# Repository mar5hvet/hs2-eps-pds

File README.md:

# hs2-eps-pds
Repository for EPS KiCad design files, including schematics, PCB layouts, and documentation.

Uploaded by Chase

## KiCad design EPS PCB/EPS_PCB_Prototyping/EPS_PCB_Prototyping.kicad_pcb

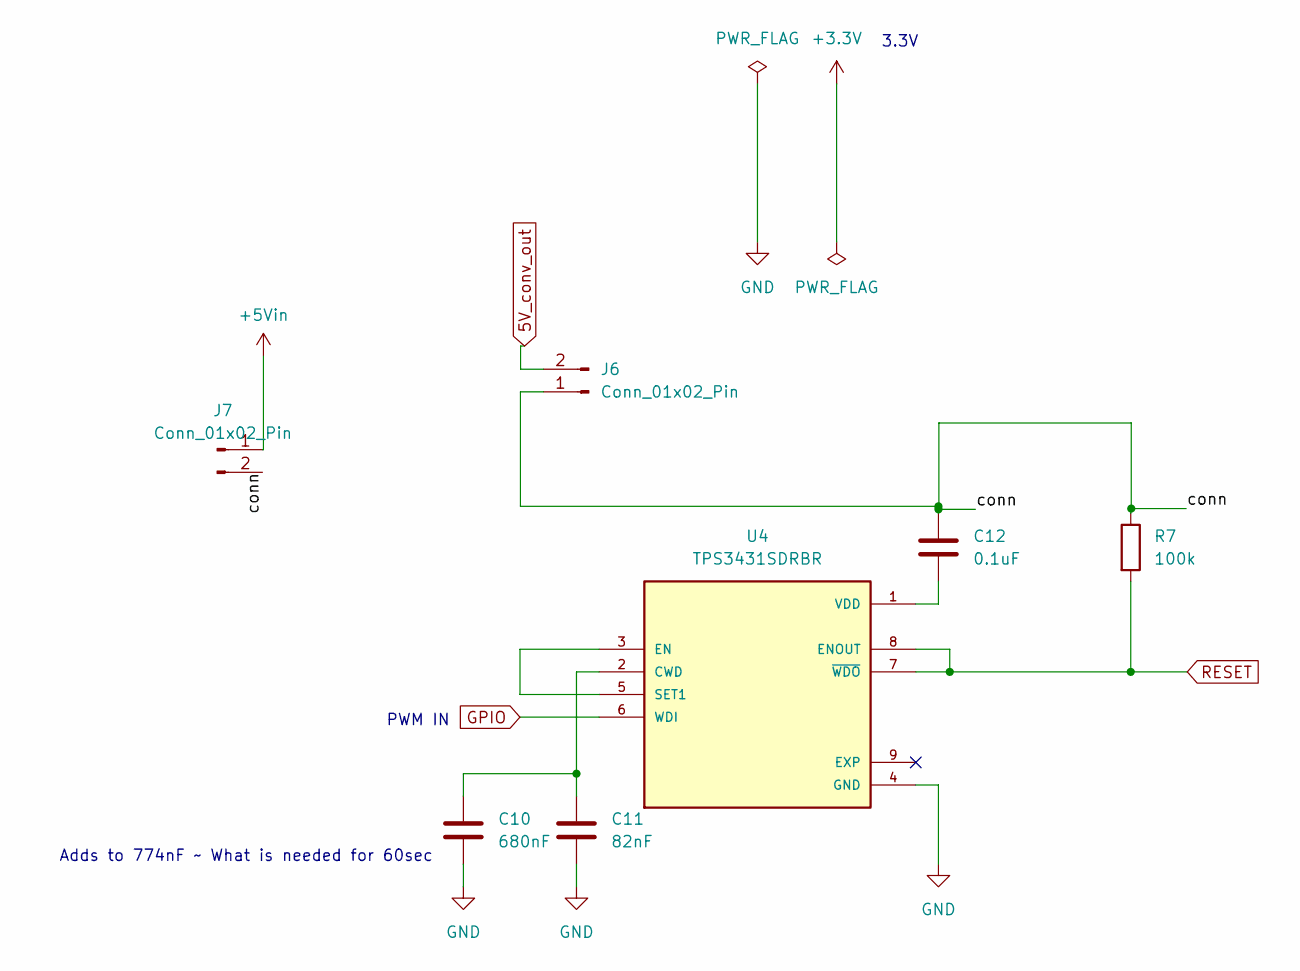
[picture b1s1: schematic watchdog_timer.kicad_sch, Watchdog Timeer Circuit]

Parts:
C10: 680nF; C_1206_3216Metric
C11: 82nF; C_1206_3216Metric
C12: 0.1uF; C_0603_1608Metric
J6, J7: Conn_01x02_Pin; PinSocket_1x02_P2.54mm_Vertical
R7: 100k; R_1206_3216Metric
U4: TPS3431SDRBR; IC_TPS3431SDRBR; PARTREV A

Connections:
5V_conv_out: J6.2; also elsewhere on the board
+5Vin: J7.1
/watchdog_timer/conn: C12.1, J6.1, J7.2, R7.1
GND: C10.2, C11.2, U4.4 (GND); also elsewhere on the board
GPIO: U4.6 (WDI); also elsewhere on the board
unnamed: C10.1, C11.1, U4.2 (CWD)
unnamed: U4.3 (EN), U4.5 (SET1)
unnamed: C12.2, U4.1 (VDD)
RESET: R7.2, U4.7 (~WDO), U4.8 (ENOUT); also elsewhere on the board

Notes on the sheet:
PWM IN
3.3V
Adds to 774nF ~ What is needed for 60sec

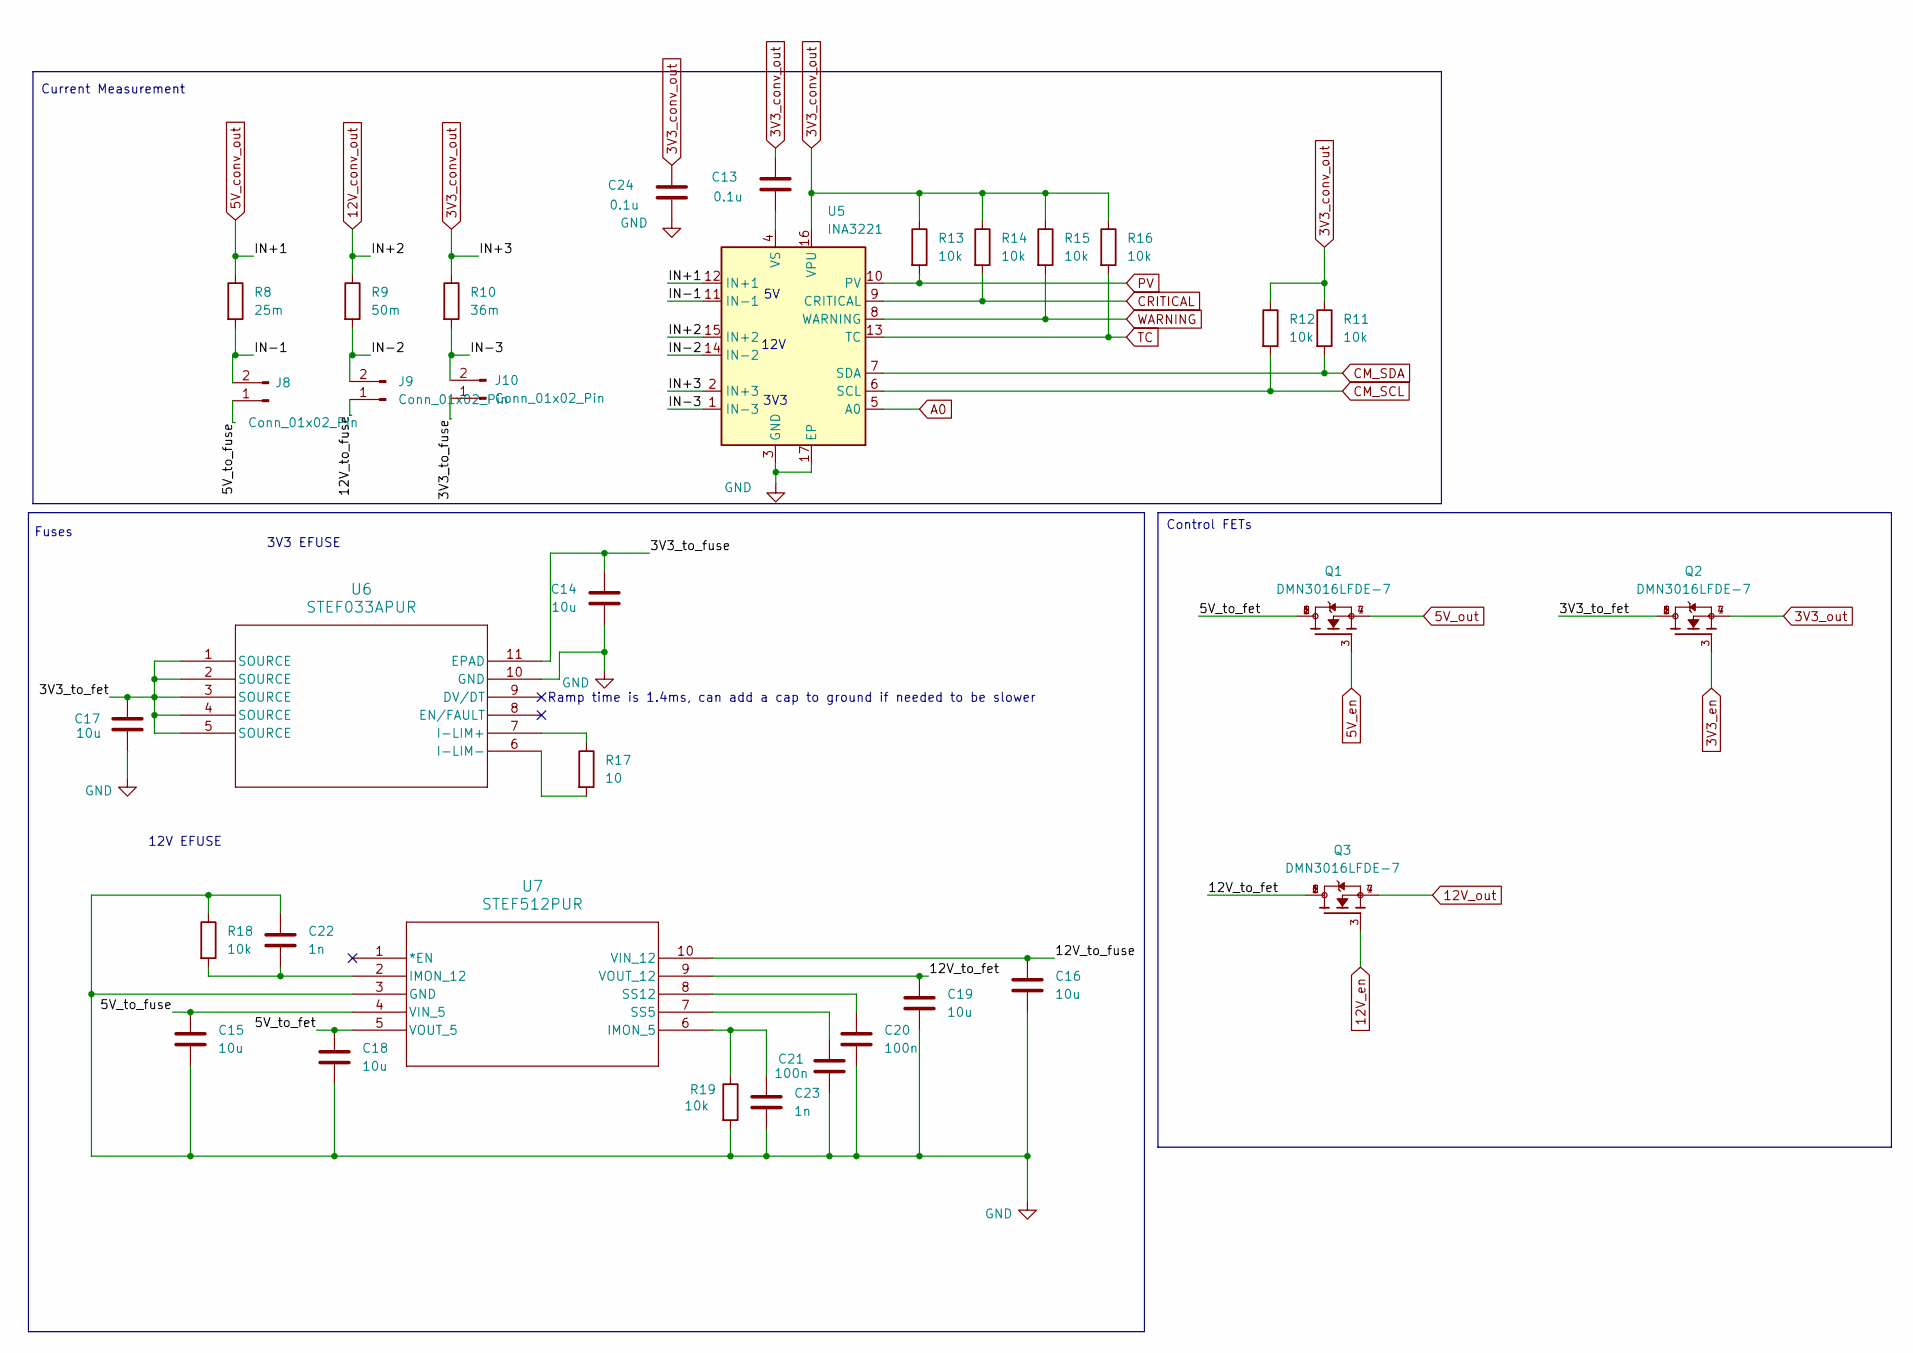
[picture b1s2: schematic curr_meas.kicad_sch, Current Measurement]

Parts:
C13, C24: 0.1u; C_0603_1608Metric
C14, C15, C16, C17, C18, C19: 10u; C_0603_1608Metric
C20, C21: 100n; C_0603_1608Metric
C22, C23: 1n; C_0603_1608Metric
J8, J9, J10: Conn_01x02_Pin; PinSocket_1x02_P2.54mm_Vertical
Q1, Q2, Q3: DMN3016LFDE-7; TRANS_DMN3016LFDE-7; PARTREV 2-2
R8: 25m; RES_VISHAY_WSLP2512_A_VIS
R9: 50m; RES_VISHAY_WSLP2512_A_VIS
R10: 36m; RES_VISHAY_WSLP2512_A_VIS
R11, R12, R13, R14, R15, R16, R18, R19: 10k; R_0603_1608Metric
R17: 10; R_0603_1608Metric
U5: INA3221; Texas_RGV0016A_VQFN-16-1EP_4x4mm_P0.65mm_EP2.1x2.1mm
U6: STEF033APUR; STEF033
U7: STEF512PUR; STEF512

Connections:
3V3_conv_out: C13.1, C24.1, R10.1, R11.1, R12.1, R13.1, R14.1, R15.1, R16.1, U5.2 (IN+3), U5.16 (VPU); also elsewhere on the board
3V3_en: Q2.3; also elsewhere on the board
3V3_out: Q2.4, Q2.7; also elsewhere on the board
5V_conv_out: R8.1, U5.12 (IN+1); also elsewhere on the board
5V_en: Q1.3; also elsewhere on the board
5V_out: Q1.4, Q1.7; also elsewhere on the board
12V_conv_out: R9.1, U5.15 (IN+2); also elsewhere on the board
12V_en: Q3.3; also elsewhere on the board
12V_out: Q3.4, Q3.7; also elsewhere on the board
/Curr_meas/3V3_to_fet: C17.1, Q2.1, Q2.2, Q2.5, Q2.6, U6.1 (SOURCE), U6.2 (SOURCE), U6.3 (SOURCE), U6.4 (SOURCE), U6.5 (SOURCE)
/Curr_meas/3V3_to_fuse: C14.1, J10.1, U6.11 (EPAD)
/Curr_meas/5V_to_fet: C18.1, Q1.1, Q1.2, Q1.5, Q1.6, U7.5 (VOUT_5)
/Curr_meas/5V_to_fuse: C15.1, J8.1, U7.4 (VIN_5)
/Curr_meas/12V_to_fet: C19.1, Q3.1, Q3.2, Q3.5, Q3.6, U7.9 (VOUT_12)
/Curr_meas/12V_to_fuse: C16.1, J9.1, U7.10 (VIN_12)
/Curr_meas/IN-1: J8.2, R8.2, U5.11 (IN-1)
/Curr_meas/IN-2: J9.2, R9.2, U5.14 (IN-2)
/Curr_meas/IN-3: J10.2, R10.2, U5.1 (IN-3)
A0: U5.5 (A0); also elsewhere on the board
CM_SCL: R12.2, U5.6 (SCL); also elsewhere on the board
CM_SDA: R11.2, U5.7 (SDA); also elsewhere on the board
CRITICAL: R14.2, U5.9 (CRITICAL); also elsewhere on the board
GND: C14.2, C15.2, C16.2, C17.2, C18.2, C19.2, C20.2, C21.2, C22.1, C23.2, C24.2, R18.1, R19.2, U5.3 (GND), U5.17 (EP), U6.10 (GND), U7.3 (GND); also elsewhere on the board
unnamed: C13.2, U5.4 (VS)
unnamed: R17.1, U6.7 (I-LIM+)
unnamed: R17.2, U6.6 (I-LIM-)
unnamed: C23.1, R19.1, U7.6 (IMON_5)
unnamed: C22.2, R18.2, U7.2 (IMON_12)
unnamed: C21.1, U7.7 (SS5)
unnamed: C20.1, U7.8 (SS12)
PV: R13.2, U5.10 (PV); also elsewhere on the board
TC: R16.2, U5.13 (TC)
WARNING: R15.2, U5.8 (WARNING); also elsewhere on the board

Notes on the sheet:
12V
Current Measurement
3V3 EFUSE
3V3
Ramp time is 1.4ms, can add a cap to ground if needed to be slower
12V EFUSE
Control FETs
Fuses

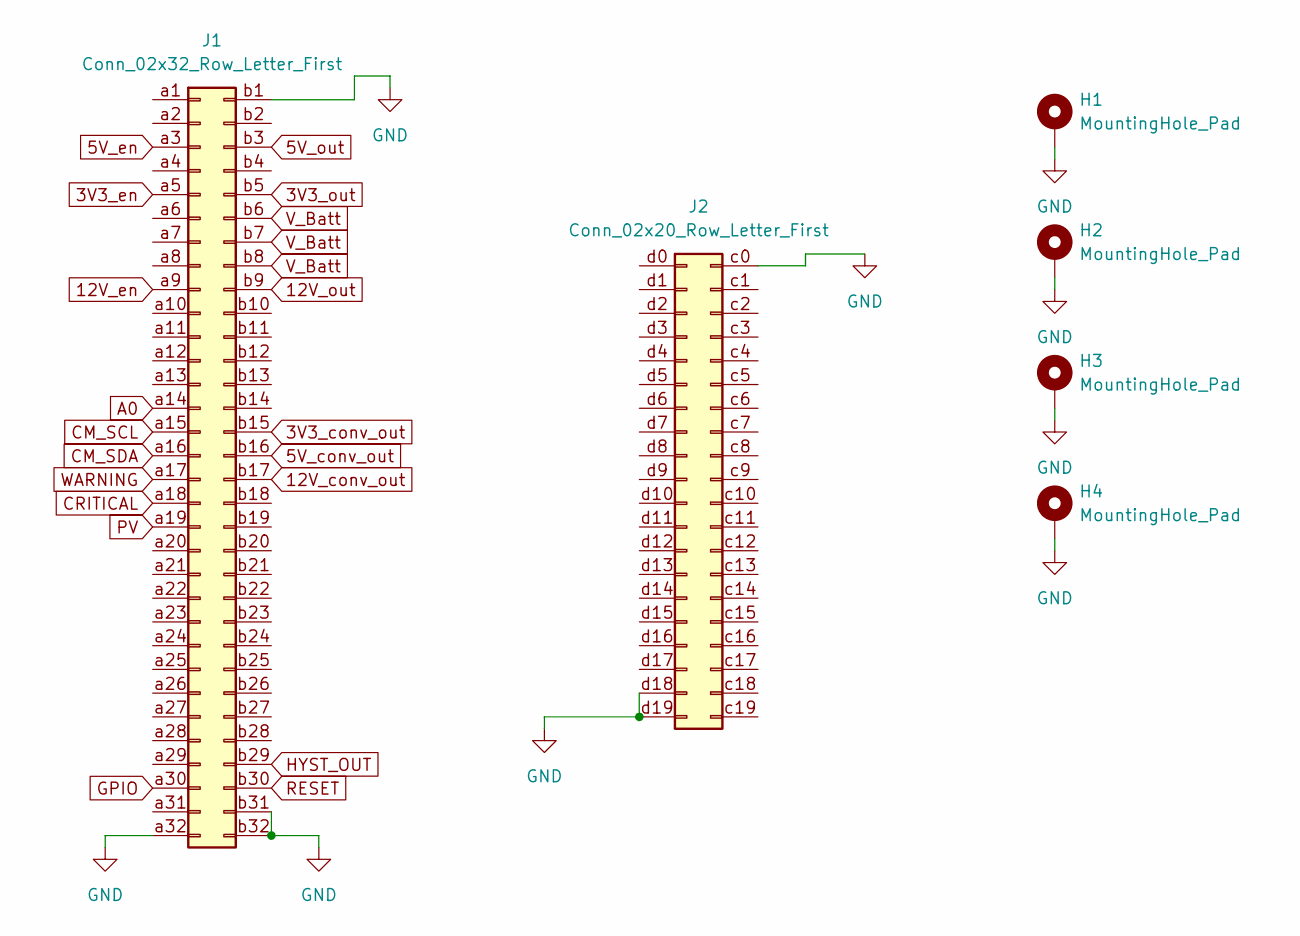
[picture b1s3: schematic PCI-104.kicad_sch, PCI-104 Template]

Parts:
H1, H2, H3, H4: MountingHole_Pad; MountingHole_3.2mm_M3_Pad
J1: Conn_02x32_Row_Letter_First; PinSocket_2x32_P2.54mm_Vertical
J2: Conn_02x20_Row_Letter_First; PinSocket_2x20_P2.54mm_Vertical

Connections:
3V3_conv_out: J1.b15; also elsewhere on the board
3V3_en: J1.a5; also elsewhere on the board
3V3_out: J1.b5; also elsewhere on the board
5V_conv_out: J1.b16; also elsewhere on the board
5V_en: J1.a3; also elsewhere on the board
5V_out: J1.b3; also elsewhere on the board
12V_conv_out: J1.b17; also elsewhere on the board
12V_en: J1.a9; also elsewhere on the board
12V_out: J1.b9; also elsewhere on the board
A0: J1.a14; also elsewhere on the board
CM_SCL: J1.a15; also elsewhere on the board
CM_SDA: J1.a16; also elsewhere on the board
CRITICAL: J1.a18; also elsewhere on the board
GND: H1.1, H2.1, H3.1, H4.1, J1.a32, J1.b1, J1.b31, J1.b32, J2.c0, J2.d18, J2.d19; also elsewhere on the board
GPIO: J1.a30; also elsewhere on the board
HYST_OUT: J1.b29; also elsewhere on the board
PV: J1.a19; also elsewhere on the board
RESET: J1.b30; also elsewhere on the board
V_Batt: J1.b6, J1.b7, J1.b8; also elsewhere on the board
WARNING: J1.a17; also elsewhere on the board

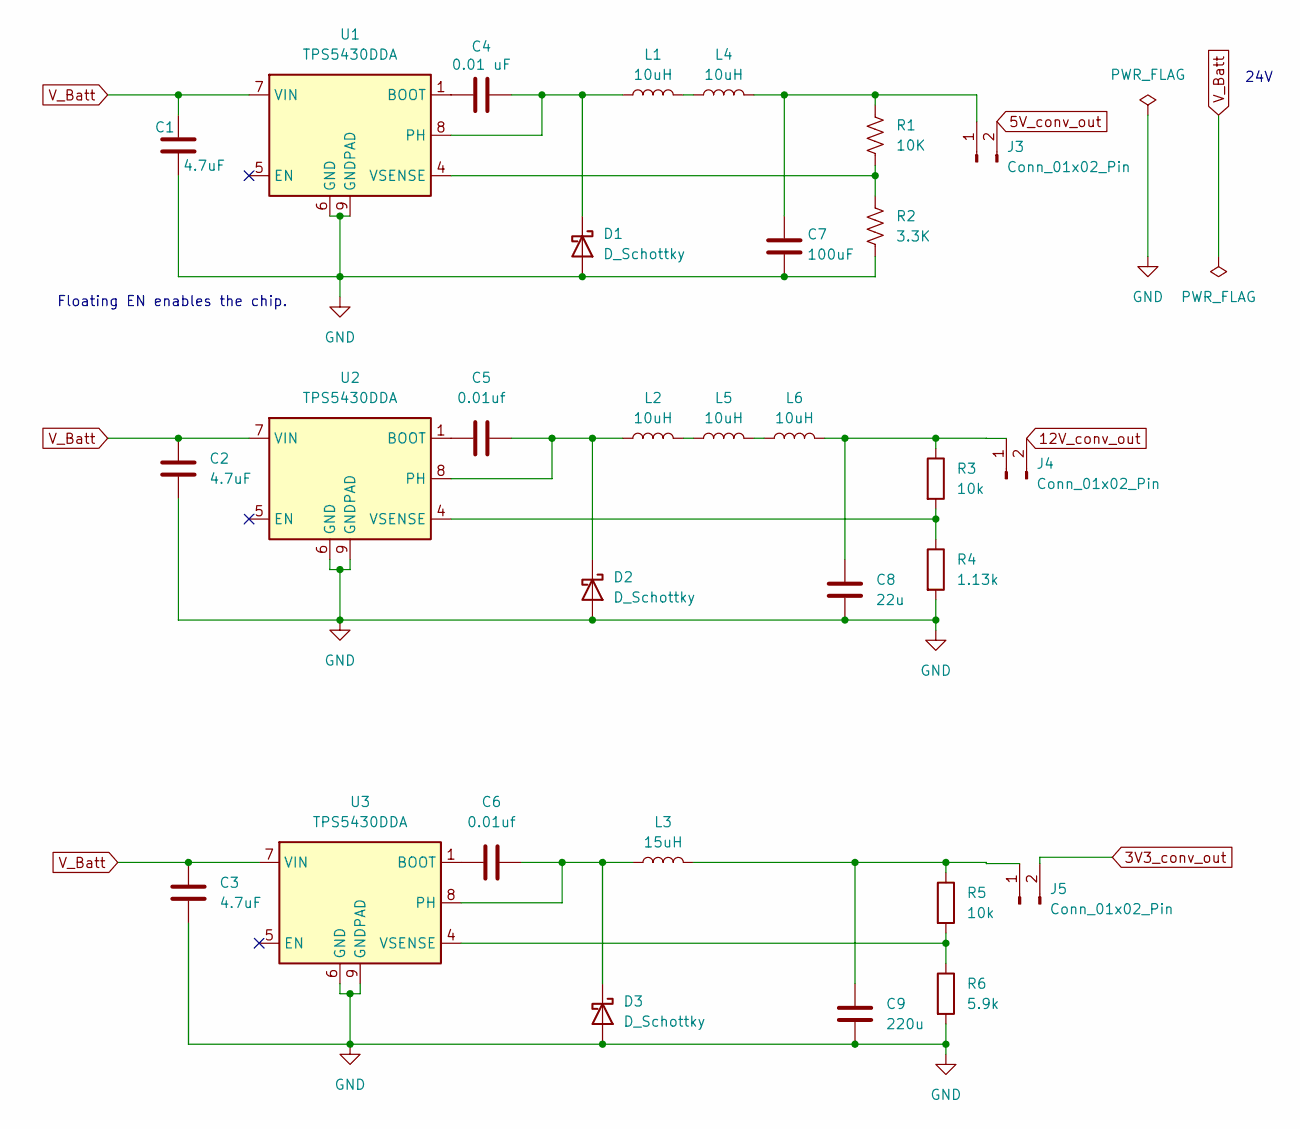
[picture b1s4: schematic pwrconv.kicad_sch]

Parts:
C1, C2, C3: 4.7uF; C_0805_2012Metric; LCSC C1779
C4: 0.01 uF; C_0603_1608Metric; LCSC C1589
C5, C6: 0.01uf; C_0603_1608Metric; LCSC C1589
C7: 100uF; C_0805_2012Metric; LCSC C2836437
C8: 22u; C_0805_2012Metric; LCSC C45783
C9: 220u; C_0805_2012Metric; LCSC C125977
D1, D2, D3: D_Schottky; D_SOD-323; LCSC C191023
J3, J4, J5: Conn_01x02_Pin; PinSocket_1x02_P2.54mm_Vertical
L1, L2, L4, L5, L6: 10uH; L_Changjiang_FXL0630; LCSC C167223
L3: 15uH; L_Changjiang_FXL0630; LCSC C40000
R1: 10K; R_0603_1608Metric; LCSC C15401
R2: 3.3K; R_1206_3216Metric; LCSC C26041
R3, R5: 10k; R_0603_1608Metric; LCSC C15401
R4: 1.13k; R_1206_3216Metric; LCSC C4410
R6: 5.9k; R_1206_3216Metric; LCSC C488883
U1, U2, U3: TPS5430DDA; TI_SO-PowerPAD-8_ThermalVias; LCSC C9864

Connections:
3V3_conv_out: J5.2; also elsewhere on the board
5V_conv_out: J3.2; also elsewhere on the board
12V_conv_out: J4.2; also elsewhere on the board
GND: C1.2, C2.2, C3.2, C7.2, C8.1, C9.1, D1.2 (A), D2.2 (A), D3.2 (A), R2.2, R4.2, R6.2, U1.6 (GND), U1.9 (GNDPAD), U2.6 (GND), U2.9 (GNDPAD), U3.6 (GND), U3.9 (GNDPAD); also elsewhere on the board
unnamed: C4.2, D1.1 (K), L1.1, U1.8 (PH)
unnamed: C5.2, D2.1 (K), L2.1, U2.8 (PH)
unnamed: C6.2, D3.1 (K), L3.1, U3.8 (PH)
unnamed: C7.1, J3.1, L4.2, R1.1
unnamed: C8.2, J4.1, L6.2, R3.1
unnamed: C9.2, J5.1, L3.2, R5.1
unnamed: L1.2, L4.1
unnamed: L2.2, L5.1
unnamed: L5.2, L6.1
unnamed: C4.1, U1.1 (BOOT)
unnamed: R1.2, R2.1, U1.4 (VSENSE)
unnamed: C5.1, U2.1 (BOOT)
unnamed: R3.2, R4.1, U2.4 (VSENSE)
unnamed: C6.1, U3.1 (BOOT)
unnamed: R5.2, R6.1, U3.4 (VSENSE)
V_Batt: C1.1, C2.1, C3.1, U1.7 (VIN), U2.7 (VIN), U3.7 (VIN); also elsewhere on the board

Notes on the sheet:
24V
Floating EN enables the chip.

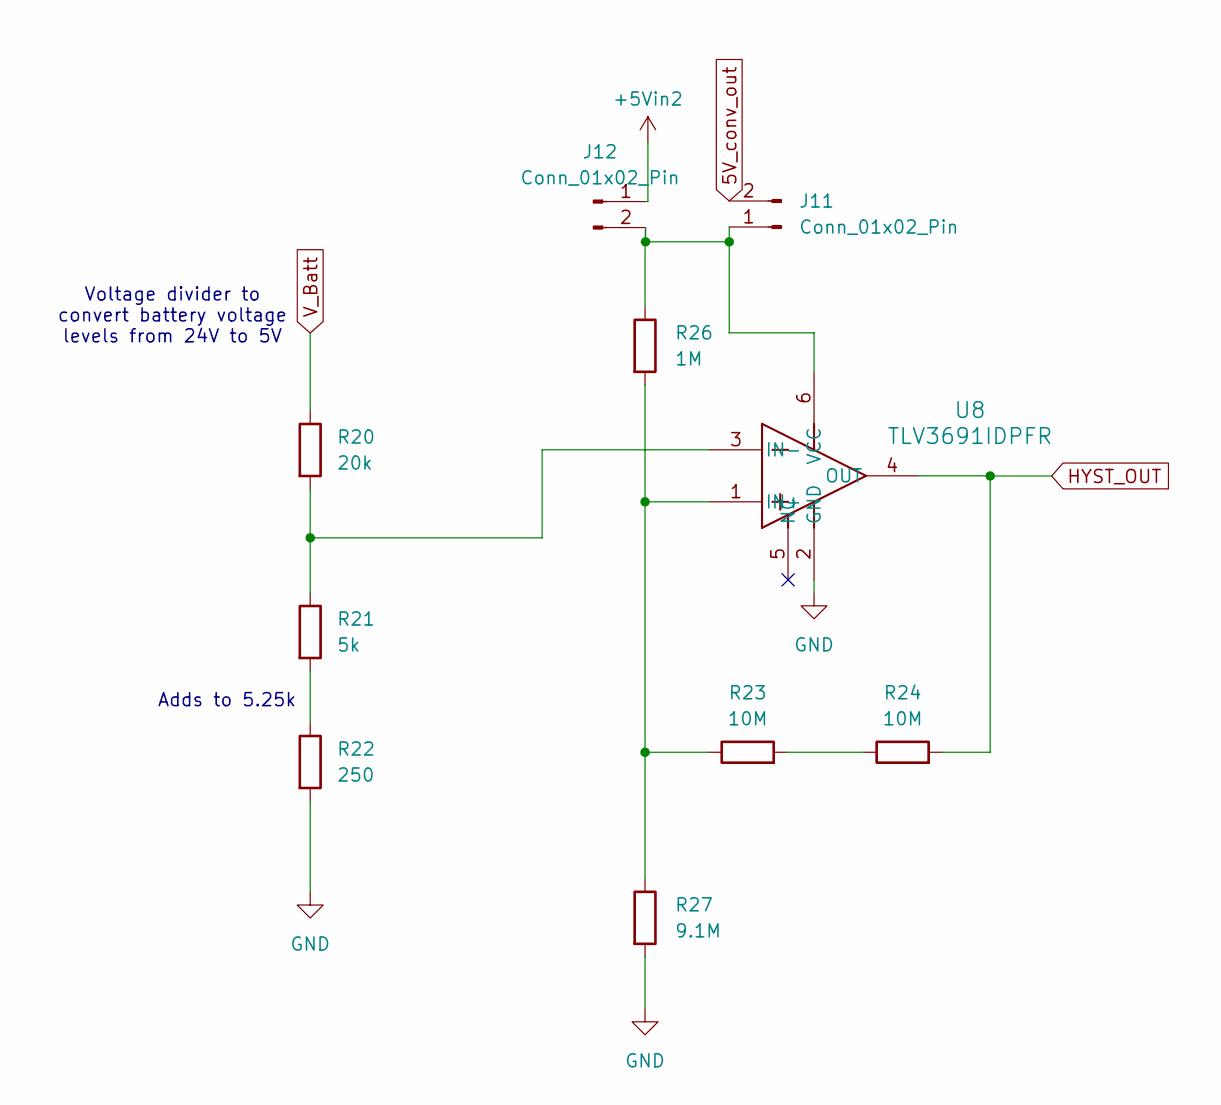
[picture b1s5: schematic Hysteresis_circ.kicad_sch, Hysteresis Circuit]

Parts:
J11, J12: Conn_01x02_Pin; PinSocket_1x02_P2.54mm_Vertical
R20: 20k; R_0603_1608Metric
R21: 5k; R_0603_1608Metric
R22: 250; R_0603_1608Metric
R23, R24: 10M; R_Axial_DIN0207_L6.3mm_D2.5mm_P7.62mm_Horizontal
R26: 1M; R_Axial_DIN0207_L6.3mm_D2.5mm_P7.62mm_Horizontal
R27: 9.1M; R_Axial_DIN0207_L6.3mm_D2.5mm_P7.62mm_Horizontal
U8: TLV3691IDPFR

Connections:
5V_conv_out: J11.2; also elsewhere on the board
+5Vin2: J12.1
GND: R22.2, R27.2, U8.2 (GND); also elsewhere on the board
HYST_OUT: R24.2, U8.4 (OUT); also elsewhere on the board
unnamed: J11.1, J12.2, R26.1, U8.6 (VCC)
unnamed: R21.2, R22.1
unnamed: R23.2, R24.1
unnamed: R23.1, R26.2, R27.1, U8.1 (IN+)
unnamed: R20.2, R21.1, U8.3 (IN-)
V_Batt: R20.1; also elsewhere on the board

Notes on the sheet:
Adds to 5.25k
Voltage divider to convert battery voltage levels from 24V to 5V

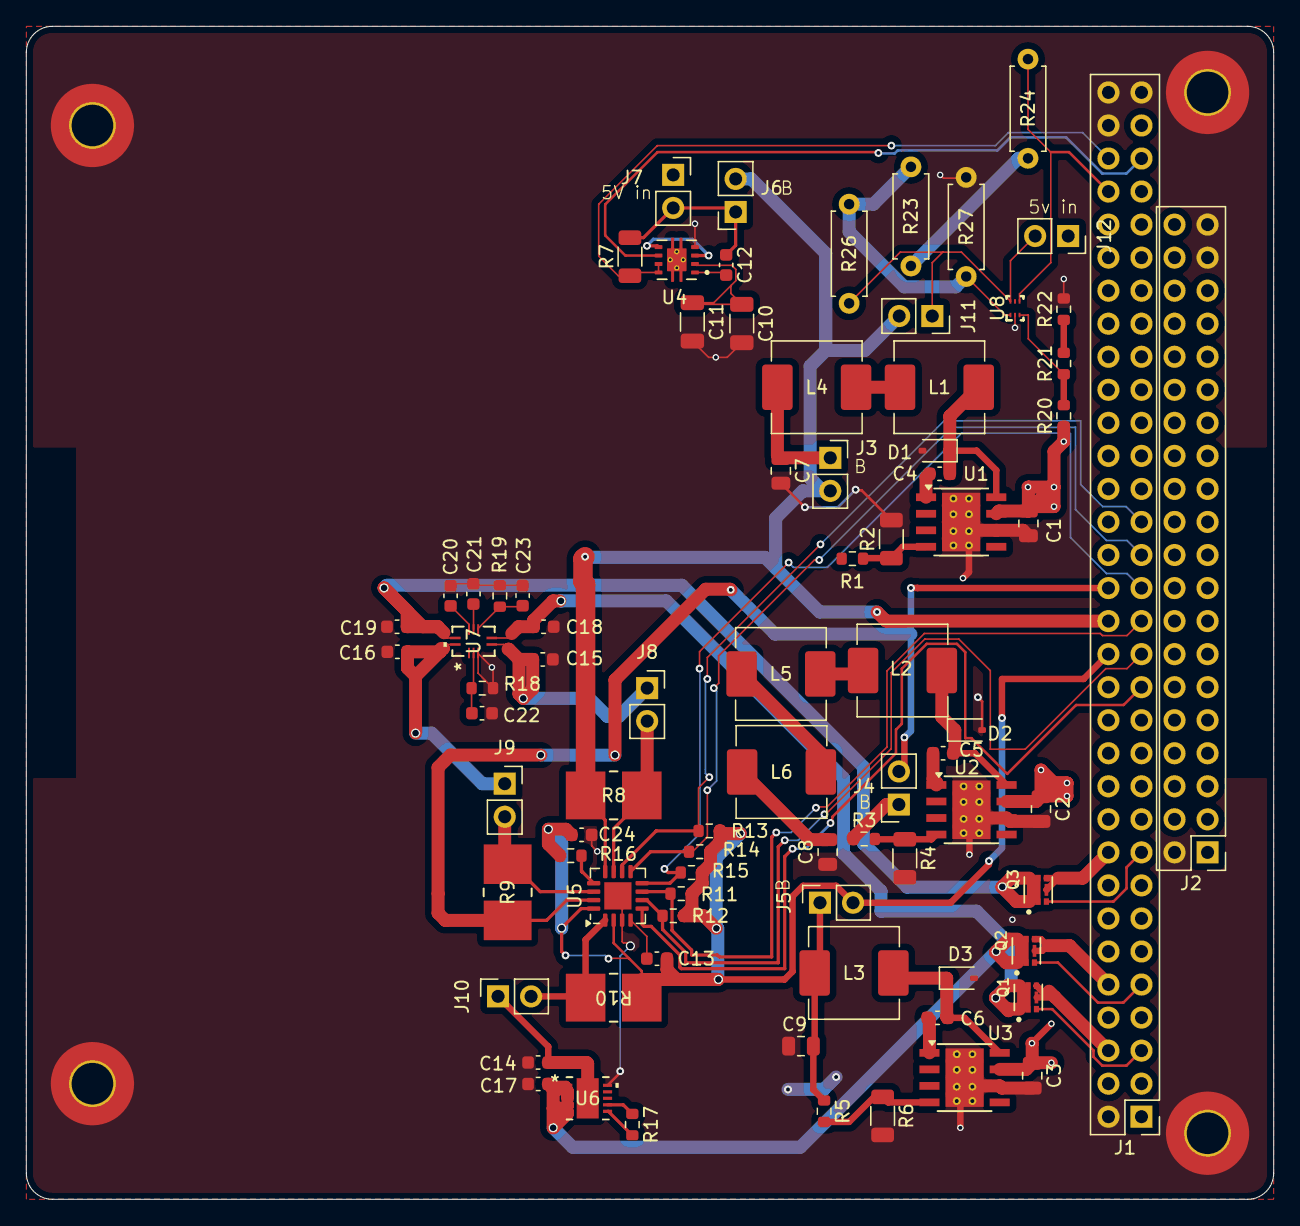
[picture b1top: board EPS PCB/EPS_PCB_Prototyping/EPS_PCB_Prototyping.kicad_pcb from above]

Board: 2 copper layers, 95.9 x 90.2 mm, 86 parts (0 on the bottom side), 61 nets.

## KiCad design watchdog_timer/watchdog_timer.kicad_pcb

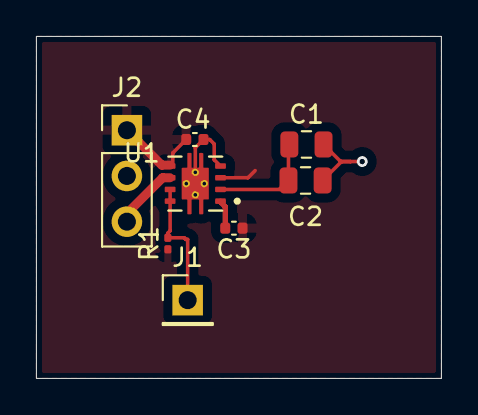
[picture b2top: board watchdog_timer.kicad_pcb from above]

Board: 2 copper layers, 22.5 x 19.0 mm, 8 parts (0 on the bottom side), 6 nets.

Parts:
C1: 680nF; C_0805_2012Metric
C2: 82nF; C_0805_2012Metric
C3, C4: 0.1uF; C_0402_1005Metric
J1: Conn_01x01_Pin; PinHeader_1x01_P2.54mm_Vertical
J2: Conn_01x03_Pin; PinHeader_1x03_P2.54mm_Vertical
R1: 100k; R_0201_0603Metric
U1: TPS3431SDRBR; IC_TPS3431SDRBR

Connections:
GND: C1.2, C2.2, C4.2, J2.2, U1.4 (GND), U1.9 (EXP), U1.10, U1.11, U1.12, U1.13
GPIO: J2.3, U1.6 (WDI)
unnamed: C1.1, C2.1, U1.2 (CWD)
unnamed: C3.2, U1.1 (VDD)
RESET: J1.1, R1.2, U1.7 (~WDO), U1.8 (ENOUT)
VDD: C3.1, C4.1, J2.1, R1.1, U1.3 (EN), U1.5 (SET1)

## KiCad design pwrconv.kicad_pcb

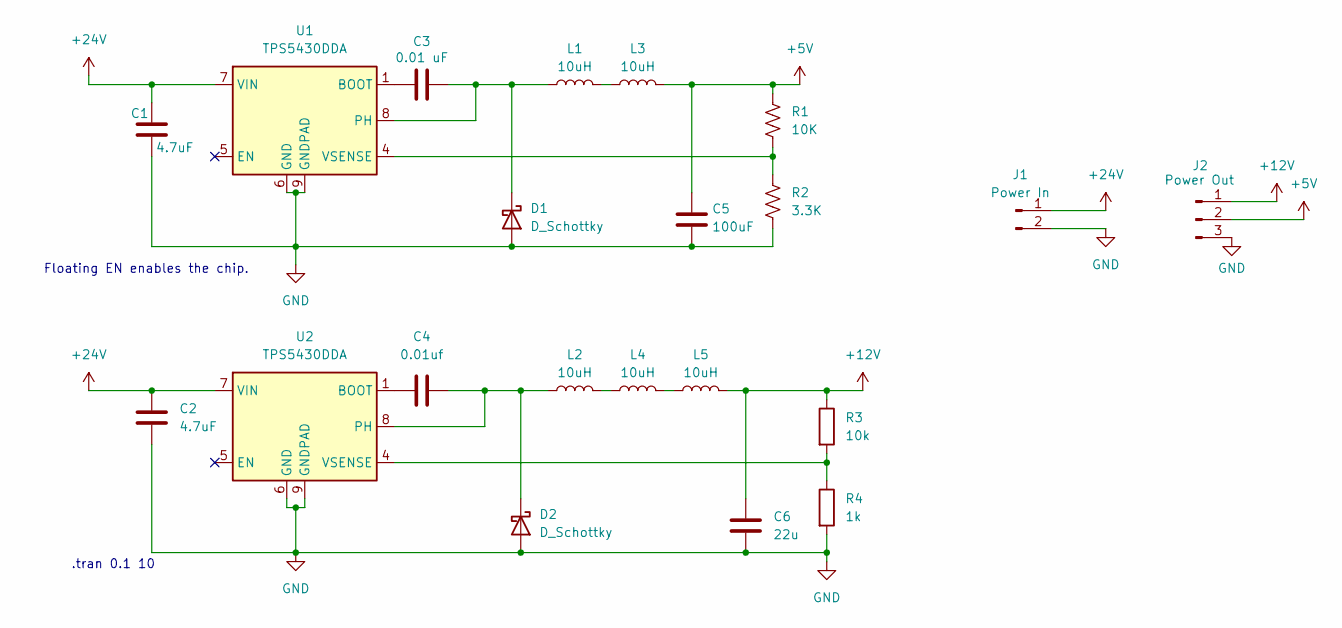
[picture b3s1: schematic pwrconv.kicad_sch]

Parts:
C1, C2: 4.7uF; C_0805_2012Metric; LCSC C1779
C3: 0.01 uF; C_0603_1608Metric; LCSC C1589
C4: 0.01uf; C_0603_1608Metric; LCSC C1589
C5: 100uF; C_Elec_6.3x7.7; LCSC C2836437
C6: 22u; C_0805_2012Metric; LCSC C45783
D1, D2: D_Schottky; D_SOD-323; LCSC C191023
J1: Power In; PinHeader_1x02_P2.54mm_Vertical
J2: Power Out; PinHeader_1x03_P2.54mm_Vertical
L1, L2, L3, L4, L5: 10uH; L_Changjiang_FXL0630; LCSC C167223
R1: 10K; R_0603_1608Metric; LCSC C15401
R2: 3.3K; R_1206_3216Metric; LCSC C26041
R3: 10k; R_0603_1608Metric; LCSC C15401
R4: 1k; R_1206_3216Metric; LCSC C4410
U1, U2: TPS5430DDA; TI_SO-PowerPAD-8_ThermalVias; LCSC C9864

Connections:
+5V: C5.1, J2.2, L3.2, R1.1
+12V: C6.2, J2.1, L5.2, R3.1
+24V: C1.1, C2.1, J1.1, U1.7 (VIN), U2.7 (VIN)
GND: C1.2, C2.2, C5.2, C6.1, D1.2 (A), D2.2 (A), J1.2, J2.3, R2.2, R4.2, U1.6 (GND), U1.9 (GNDPAD), U2.6 (GND), U2.9 (GNDPAD)
unnamed: C3.2, D1.1 (K), L1.1, U1.8 (PH)
unnamed: C4.2, D2.1 (K), L2.1, U2.8 (PH)
unnamed: L1.2, L3.1
unnamed: L2.2, L4.1
unnamed: L4.2, L5.1
unnamed: C3.1, U1.1 (BOOT)
unnamed: R1.2, R2.1, U1.4 (VSENSE)
unnamed: C4.1, U2.1 (BOOT)
unnamed: R3.2, R4.1, U2.4 (VSENSE)

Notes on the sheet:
Floating EN enables the chip.
.tran 0.1 10

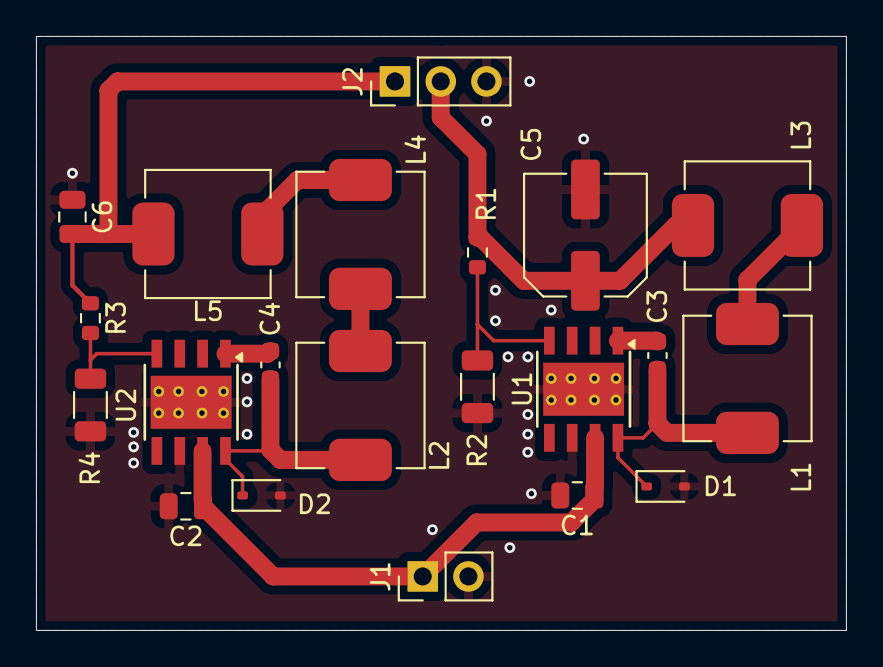
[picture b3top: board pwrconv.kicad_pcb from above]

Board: 2 copper layers, 45.0 x 33.0 mm, 21 parts (0 on the bottom side), 13 nets.

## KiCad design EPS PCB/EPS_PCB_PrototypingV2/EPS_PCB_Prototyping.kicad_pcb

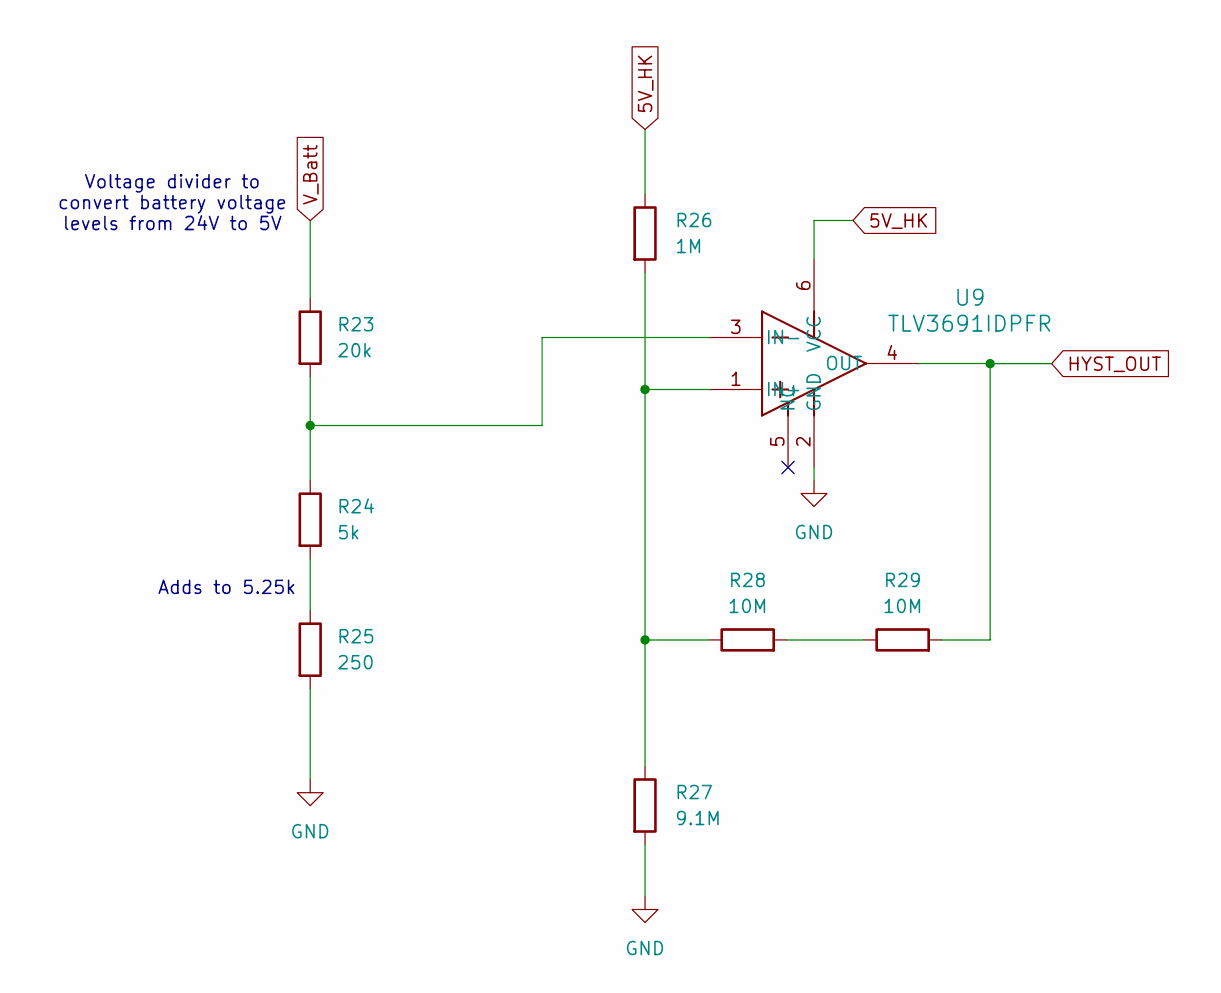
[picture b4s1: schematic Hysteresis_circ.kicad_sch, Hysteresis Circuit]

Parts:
R23: 20k; R_0603_1608Metric
R24: 5k; R_0603_1608Metric
R25: 250; R_0603_1608Metric
R26: 1M; R_1206_3216Metric
R27: 9.1M; R_1206_3216Metric
R28, R29: 10M; R_1206_3216Metric
U9: TLV3691IDPFR

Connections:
5V_HK: R26.1, U9.6 (VCC); also elsewhere on the board
GND: R25.2, R27.2, U9.2 (GND); also elsewhere on the board
HYST_OUT: R29.2, U9.4 (OUT)
unnamed: R24.2, R25.1
unnamed: R28.2, R29.1
unnamed: R26.2, R27.1, R28.1, U9.1 (IN+)
unnamed: R23.2, R24.1, U9.3 (IN-)
V_Batt: R23.1; also elsewhere on the board

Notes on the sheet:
Adds to 5.25k
Voltage divider to convert battery voltage levels from 24V to 5V

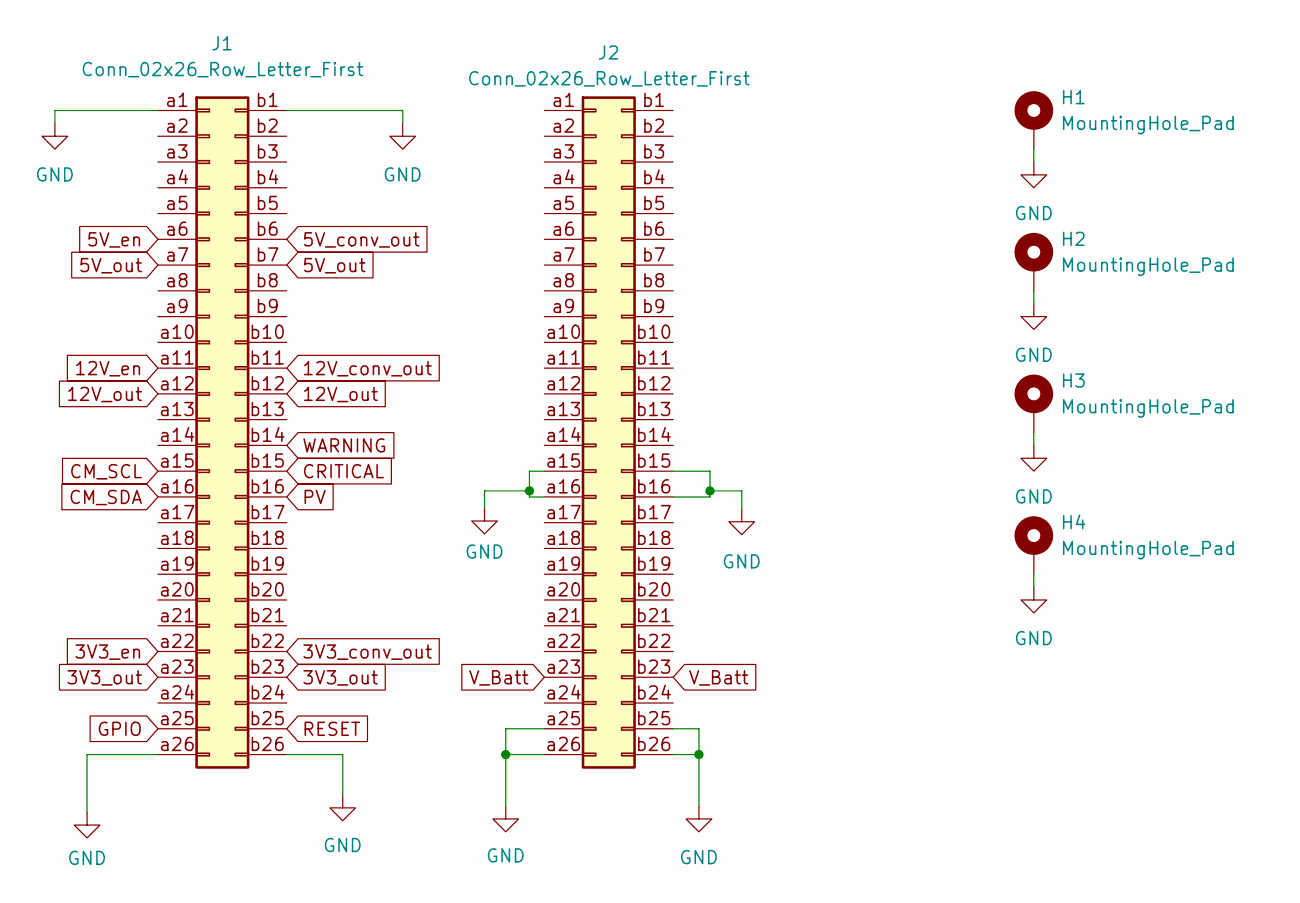
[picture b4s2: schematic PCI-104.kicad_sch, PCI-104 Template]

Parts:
H1, H2, H3, H4: MountingHole_Pad; MountingHole_3.2mm_M3_Pad
J1, J2: Conn_02x26_Row_Letter_First; PinSocket_2x26_P2.54mm_Vertical

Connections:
3V3_conv_out: J1.b22; also elsewhere on the board
3V3_en: J1.a22; also elsewhere on the board
3V3_out: J1.a23, J1.b23; also elsewhere on the board
5V_conv_out: J1.b6; also elsewhere on the board
5V_en: J1.a6; also elsewhere on the board
5V_out: J1.a7, J1.b7; also elsewhere on the board
12V_conv_out: J1.b11; also elsewhere on the board
12V_en: J1.a11; also elsewhere on the board
12V_out: J1.a12, J1.b12; also elsewhere on the board
CM_SCL: J1.a15; also elsewhere on the board
CM_SDA: J1.a16; also elsewhere on the board
CRITICAL: J1.b15; also elsewhere on the board
GND: H1.1, H2.1, H3.1, H4.1, J1.a1, J1.a26, J1.b1, J1.b26, J2.a15, J2.a16, J2.a25, J2.a26, J2.b15, J2.b16, J2.b25, J2.b26; also elsewhere on the board
GPIO: J1.a25; also elsewhere on the board
PV: J1.b16; also elsewhere on the board
RESET: J1.b25; also elsewhere on the board
V_Batt: J2.a23, J2.b23; also elsewhere on the board
WARNING: J1.b14; also elsewhere on the board
